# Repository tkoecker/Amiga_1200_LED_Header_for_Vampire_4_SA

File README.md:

# Amiga 1200 LED Header for Vampire 4 Standalone

I've printed the fantastic Vampire 4 Standalone enclosure by Jörgen Bilander (see https://github.com/jbilander/Vampire_V4_Standalone_Enclosure). It allows to mount an Amiga 1200 LED PCB, however the Vampire 4 SA does not have any header to connect this board. This is why I've made a small adapter PCB that adds an Amiga 1200 LED header to the Vampire 4 SA.

(LED activity in the image above: Power on, SD card access to load kick rom, Amiga OS booting, Amiga OS mounting/reading SD card)

It uses an IC that provides 4 opamps. One opamp each is used to sense the power and drive LED state, adding only a neglectable additional load to the outputs of the V4SA. The two remaining opamps are for the floppy LED which can be either be triggered from an active low or an active high signal (selectable using a solder jumper).
The chosen opamps have rail-to-rail outputs which allows to drive the LEDs on the Amiga 1200 LED PCB with a similar voltage as the original Amiga 1200 circuitry.

*WARNING:* There is some fine soldering needed to install the PCB on the V4SA. If you do not feel confident doing that, please ask somebody who does. It would be a pitty if you ruin your nice V4SA when installing this board.

Adapter (please note that the images were taken from an old board version, the current one has less solder pads - they are not needed):

The board sits on top of the 68000 pins of the Vampire 4 SA and gets +5V and GND from there.

It also needs two wires to the original power and drive LEDs of the V4SA to sense their state.

For using the floppy led for the micro-SD card access a wire to pin 2 of the micro-SD card slot of the V4SA is needed.

If you want use the floppy led you need to connect a solder jumper to select whether the signal is active-low or active-high:

[Link to PCB on PCBWay](https://www.pcbway.com/project/shareproject/Amiga_1200_LED_Header_for_Vampire_4_Standalone.html)

BOM:
- R1, R2: 82 kOhm 0805 SMD resistor
- IC1: TLV2774CD
- 5V/GND pins: 1 pin of a straight pin header each
- LED pin header: 5 pin angled pin header

Images:

***DISCLAIMER:***

This hardware/software is provided "as is", and you use the hardware/software at your own risk. Under no circumstances shall any author be liable for direct, indirect, special, incidental, or consequential damages resulting from the use, misuse, or inability to use this hardware/software, even if the authors have been advised of the possibility of such damages.

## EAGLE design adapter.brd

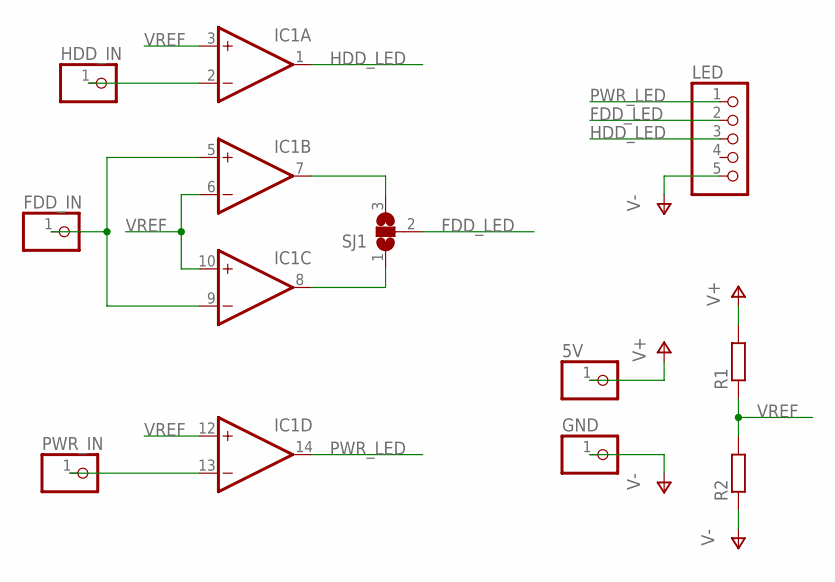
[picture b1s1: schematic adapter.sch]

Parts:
5V: PINHD-1X1; 1X01
FDD_IN: PINHD-1X1; 1X01
GND: PINHD-1X1; 1X01
HDD_IN: PINHD-1X1; 1X01
IC1: OP11D; SO14
LED: PINHD-1X5; 1X05
PWR_IN: PINHD-1X1; 1X01
R1, R2: R-EU_R0805; R0805
SJ1: SJ2W; SJ_2

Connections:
FDD_IN: FDD_IN.1, IC1.5 (+IN), IC1.9 (-IN)
FDD_LED: LED.2, SJ1.2
HDD_IN: HDD_IN.1, IC1.2 (-IN)
HDD_LED: IC1.1 (OUT), LED.3
unnamed: IC1.7 (OUT), SJ1.3
unnamed: IC1.8 (OUT), SJ1.1
PWR_IN: IC1.13 (-IN), PWR_IN.1
PWR_LED: IC1.14 (OUT), LED.1
V+: 5V.1, IC1.4 (V+), R1.2
V-: GND.1, IC1.11 (V-), LED.5, R2.1
VREF: IC1.3 (+IN), IC1.6 (-IN), IC1.10 (+IN), IC1.12 (+IN), R1.1, R2.2

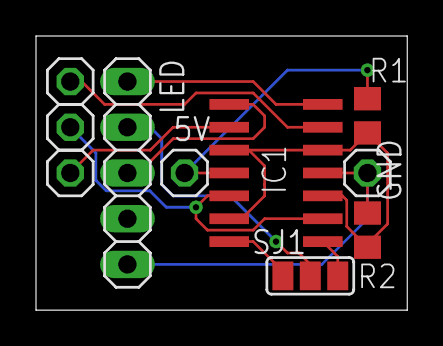
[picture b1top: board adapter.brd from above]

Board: 2 copper layers, 20.6 x 15.2 mm, 10 parts (0 on the bottom side), 11 nets.

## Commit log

2020-07-29 replaced anim
2020-08-06 added info about wires and solder jumper
2021-09-24 added description for usb port upgrade
